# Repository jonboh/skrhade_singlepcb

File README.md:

# SKRHADE010 Single PCB
These PCBs were designed to iterate on a [dactyl design mounting these switches](https://github.com/jonboh/skyl_prototype).

These switches can be acquired in [Mouser](https://eu.mouser.com/ProductDetail/688-SKRHAD) and probably other electronic component stores.

The file [skrhade_fabrication.zip](./skrhade_fabrication.zip) can be used to
order a set of these. Note however that design i not very good, in the effort
of making the footprint as small as possible I did not realize that the wiring would be much easier
if there were pads for each point (R1, R2, R3, R4, R5, CN) on both sides. Otherwise you need a common
point for all switches. I fixed this by soldering all wires to a central point and using hot glue as
insulator.

I did not continue with the Skyl project, otherwise I would have
made the change in the design and ordered a new set.

If you want to continue with the design, I would advise adding a bit more vertical space to the PCB
and adding the missing pads of both sides, wiring will be much easier, and similar to the [single
pcbs](https://github.com/jonboh/amoeba-cherry-ulp?tab=readme-ov-file#back) used in keyboard desings with typical switches.

This project was inspired by the [harite](https://github.com/dlip/harite), I used its footprints for the single PCB.

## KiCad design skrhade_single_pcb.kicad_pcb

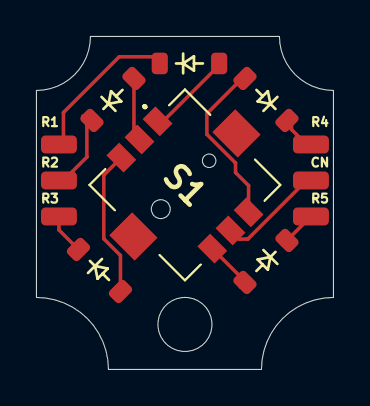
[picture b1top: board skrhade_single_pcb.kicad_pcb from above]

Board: 2 copper layers, 16.5 x 18.5 mm, 12 parts (0 on the bottom side), 11 nets.

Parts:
CN: C; SolderWirePad_1x01_SMD_1x2mm
D1, D2, D3, D4, D5: D; Diode_SOD-123
R1: R1; SolderWirePad_1x01_SMD_1x2mm
R2, R3: R2; SolderWirePad_1x01_SMD_1x2mm
R4: R4; SolderWirePad_1x01_SMD_1x2mm
R5: R5; SolderWirePad_1x01_SMD_1x2mm
S1: SKRHADE010; SKRHADE

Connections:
Col N: CN.1, S1.5 (COMMON)
unnamed: D1.2 (A), S1.1 (A)
unnamed: D2.2 (A), S1.2 (CENTER)
unnamed: D3.2 (A), S1.3 (C)
unnamed: D4.2 (A), S1.4 (B)
unnamed: D5.2 (A), S1.6 (D)
Row 1: D1.1 (K), R1.1
Row 2: D2.1 (K), R2.1
Row 3: D3.1 (K), R3.1
Row 4: D4.1 (K), R4.1
Row 5: D5.1 (K), R5.1

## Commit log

2024-10-03 first fabrication
2025-01-12 Create LICENSE
2025-01-12 add readme
